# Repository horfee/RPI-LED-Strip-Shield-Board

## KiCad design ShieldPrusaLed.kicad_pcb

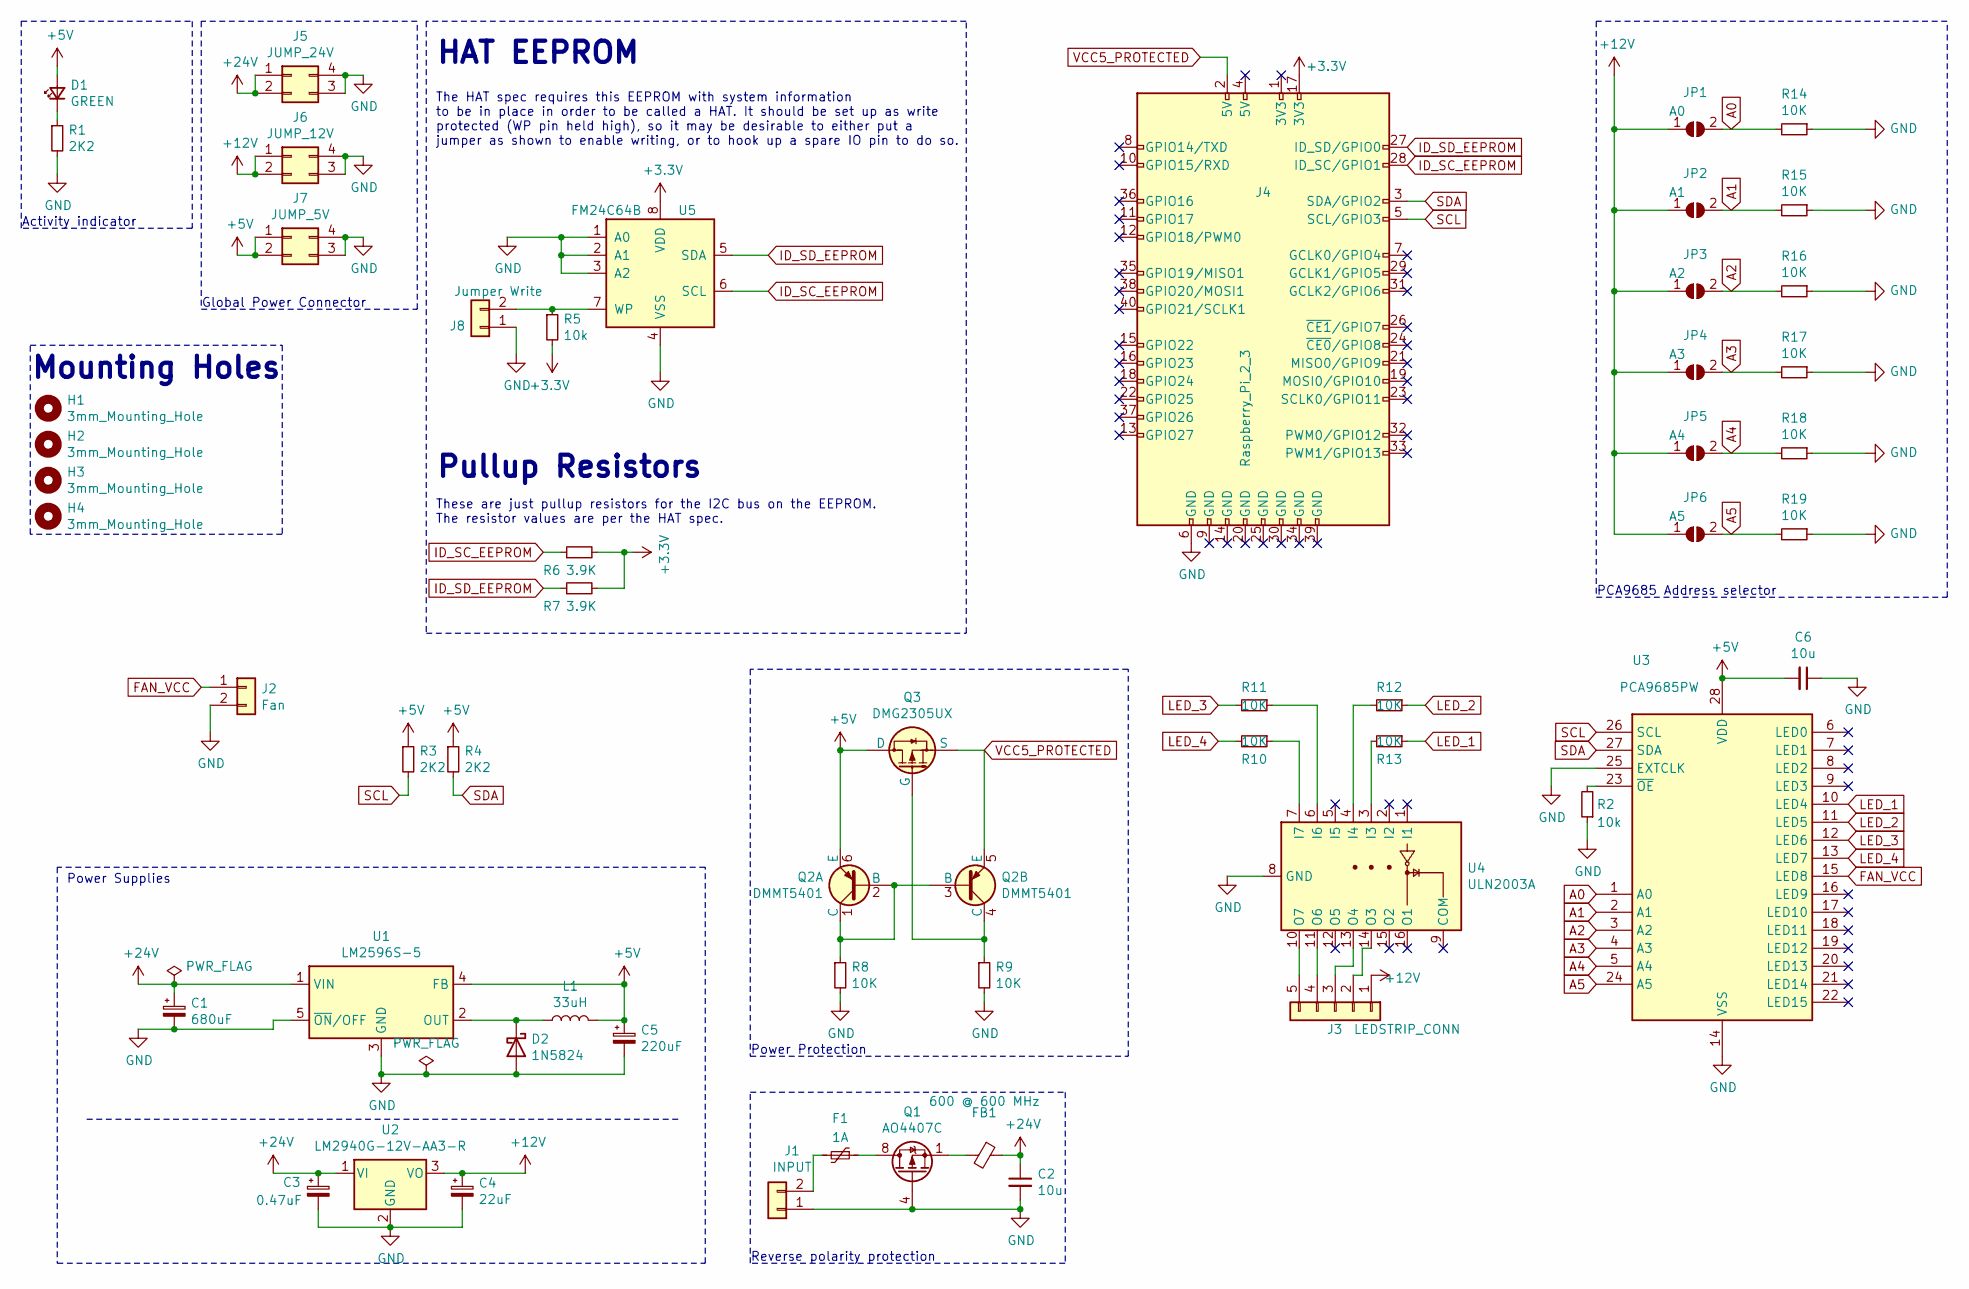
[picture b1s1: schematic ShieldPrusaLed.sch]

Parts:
C1: 680uF; CP_Radial_D10.0mm_P5.00mm_P7.50mm
C2, C6: 10u; C_0805_2012Metric
C3: 0.47uF; C_0603_1608Metric
C4: 22uF; C_0805_2012Metric
C5: 220uF; CP_Elec_6.3x5.4
D1: GREEN; LED_0603_1608Metric
D2: 1N5824; D_SMA
F1: 1A; Fuse_1206_3216Metric
FB1: 600 @ 600 MHz; R_0805_2012Metric
H1, H2, H3, H4: 3mm_Mounting_Hole; NPTH_3mm_ID
J1: INPUT; TerminalBlock_bornier-2_P5.08mm
J2: Fan; PinHeader_2x01_P2.54mm_Vertical_SMD
J3: LEDSTRIP_CONN; PinHeader_1x05_P2.54mm_Vertical_SMD_Pin1Left
J4: Raspberry_Pi_2_3; PinHeader_2x20_P2.54mm_Vertical_SMD
J5: JUMP_24V; PinHeader_2x02_P2.54mm_Vertical_SMD
J6: JUMP_12V; PinHeader_2x02_P2.54mm_Vertical_SMD
J7: JUMP_5V; PinHeader_2x02_P2.54mm_Vertical_SMD
J8: Jumper Write; PinHeader_2x01_P2.54mm_Vertical_SMD
JP1: A0; SolderJumper-2_P1.3mm_Open_RoundedPad1.0x1.5mm
JP2: A1; SolderJumper-2_P1.3mm_Open_RoundedPad1.0x1.5mm
JP3: A2; SolderJumper-2_P1.3mm_Open_RoundedPad1.0x1.5mm
JP4: A3; SolderJumper-2_P1.3mm_Open_RoundedPad1.0x1.5mm
JP5: A4; SolderJumper-2_P1.3mm_Open_RoundedPad1.0x1.5mm
JP6: A5; SolderJumper-2_P1.3mm_Open_RoundedPad1.0x1.5mm
L1: 33uH; L_12x12mm_H8mm
Q1: AO4407C; SOP-8_3.9x4.9mm_P1.27mm
Q2: DMMT5401; SOT-23-6
Q3: DMG2305UX; SOT-23
R1: 2K2; R_0402_1005Metric
R2, R5: 10k; R_0402_1005Metric
R3, R4: 2K2; R_0603_1608Metric
R6, R7: 3.9K; R_0603_1608Metric
R8, R9, R10, R11, R12, R13, R14, R15, R16, R17, R18, R19: 10K; R_0402_1005Metric
U1: LM2596S-5; TO-263-5_TabPin3
U2: LM2940G-12V-AA3-R; SOT-223
U3: PCA9685PW; TSSOP-28_4.4x9.7mm_P0.65mm
U4: ULN2003A; SOP-16_3.9x9.9mm_P1.27mm
U5: FM24C64B; SOIC-8_3.9x4.9mm_P1.27mm

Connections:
+3V3: J4.17 (3V3), R5.2, R6.2, R7.2, U5.8 (VDD); also elsewhere on the board
+5V: C5.1, C6.2, D1.2 (A), J7.1, J7.2, L1.2, Q2.6 (E), Q3.3 (D), R3.1, R4.1, U1.4 (FB), U3.28 (VDD)
+12V: C4.1, J3.1, J6.1, J6.2, JP1.1 (A), JP2.1 (A), JP3.1 (A), JP4.1 (A), JP5.1 (A), JP6.1 (A), U2.3 (VO)
+24V: C1.1, C2.1, C3.1, FB1.1, J5.1, J5.2, U1.1 (VIN), U2.1 (VI)
A0: JP1.2 (B), R14.2, U3.1 (A0)
A1: JP2.2 (B), R15.2, U3.2 (A1)
A2: JP3.2 (B), R16.2, U3.3 (A2)
A3: JP4.2 (B), R17.2, U3.4 (A3)
A4: JP5.2 (B), R18.2, U3.5 (A4)
A5: JP6.2 (B), R19.2, U3.24 (A5)
FAN_VCC: J2.1, U3.15 (LED8)
GND: C1.2, C2.2, C3.2, C4.2, C5.2, C6.1, D2.2 (A), J1.1, J2.2, J4.6 (GND), J5.3, J5.4, J6.3, J6.4, J7.3, J7.4, J8.1, Q1.4 (G), R1.2, R2.1, R8.2, R9.2, R14.1, R15.1, R16.1, R17.1, R18.1, R19.1, U1.3 (GND), U1.5 (~ON~/OFF), U2.2 (GND), U3.14 (VSS), U3.25 (EXTCLK), U4.8 (GND), U5.1 (A0), U5.2 (A1), U5.3 (A2), U5.4 (VSS); also elsewhere on the board
ID_SC_EEPROM: J4.28 (ID_SC/GPIO1), R6.1, U5.6 (SCL); also elsewhere on the board
ID_SD_EEPROM: J4.27 (ID_SD/GPIO0), R7.1, U5.5 (SDA); also elsewhere on the board
LED_1: R13.1, U3.10 (LED4)
LED_2: R12.1, U3.11 (LED5)
LED_3: R11.2, U3.12 (LED6)
LED_4: R10.2, U3.13 (LED7)
unnamed: D1.1 (K), R1.1
unnamed: D2.1 (K), L1.1, U1.2 (OUT)
unnamed: F1.1, Q1.8 (D)
unnamed: F1.2, J1.2
unnamed: FB1.2, Q1.1 (S)
unnamed: J3.2, U4.14 (O3)
unnamed: J3.3, U4.13 (O4)
unnamed: J3.4, U4.11 (O6)
unnamed: J3.5, U4.10 (O7)
unnamed 27: J4.1 (3V3); also elsewhere on the board
unnamed 28: J4.4 (5V); also elsewhere on the board
unnamed 29: J4.7 (GCLK0/GPIO4); also elsewhere on the board
unnamed 30: J4.8 (GPIO14/TXD); also elsewhere on the board
unnamed 31: J4.9 (GND); also elsewhere on the board
unnamed 32: J4.10 (GPIO15/RXD); also elsewhere on the board
unnamed 33: J4.11 (GPIO17); also elsewhere on the board
unnamed 34: J4.12 (GPIO18/PWM0); also elsewhere on the board
unnamed 35: J4.13 (GPIO27); also elsewhere on the board
unnamed 36: J4.14 (GND); also elsewhere on the board
unnamed 37: J4.15 (GPIO22); also elsewhere on the board
unnamed 38: J4.16 (GPIO23); also elsewhere on the board
unnamed 39: J4.18 (GPIO24); also elsewhere on the board
unnamed 40: J4.19 (MOSI0/GPIO10); also elsewhere on the board
unnamed 41: J4.20 (GND); also elsewhere on the board
unnamed 42: J4.21 (MISO0/GPIO9); also elsewhere on the board
unnamed 43: J4.22 (GPIO25); also elsewhere on the board
unnamed 44: J4.23 (SCLK0/GPIO11); also elsewhere on the board
unnamed 45: J4.24 (~CE0~/GPIO8); also elsewhere on the board
unnamed 46: J4.25 (GND); also elsewhere on the board
unnamed 47: J4.26 (~CE1~/GPIO7); also elsewhere on the board
unnamed 48: J4.29 (GCLK1/GPIO5); also elsewhere on the board
unnamed 49: J4.30 (GND); also elsewhere on the board
unnamed 50: J4.31 (GCLK2/GPIO6); also elsewhere on the board
unnamed 51: J4.32 (PWM0/GPIO12); also elsewhere on the board
unnamed 52: J4.33 (PWM1/GPIO13); also elsewhere on the board
unnamed 53: J4.34 (GND); also elsewhere on the board
unnamed 54: J4.35 (GPIO19/MISO1); also elsewhere on the board
unnamed 55: J4.36 (GPIO16); also elsewhere on the board
unnamed 56: J4.37 (GPIO26); also elsewhere on the board
unnamed 57: J4.38 (GPIO20/MOSI1); also elsewhere on the board
unnamed 58: J4.39 (GND); also elsewhere on the board
unnamed 59: J4.40 (GPIO21/SCLK1); also elsewhere on the board
unnamed: J8.2, R5.1, U5.7 (WP)
unnamed: Q2.1 (C), Q2.2 (B), Q2.3 (B), R8.1
unnamed: Q2.4 (C), Q3.1 (G), R9.1
unnamed: R2.2, U3.23 (~OE)
unnamed: R10.1, U4.7 (I7)
unnamed: R11.1, U4.6 (I6)
unnamed: R12.2, U4.4 (I4)
unnamed: R13.2, U4.3 (I3)
SCL: J4.5 (SCL/GPIO3), R3.2, U3.26 (SCL); also elsewhere on the board
SDA: J4.3 (SDA/GPIO2), R4.2, U3.27 (SDA); also elsewhere on the board
VCC5_PROTECTED: J4.2 (5V), Q2.5 (E), Q3.2 (S); also elsewhere on the board

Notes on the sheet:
Reverse polarity protection
Activity indicator
Power Supplies
Global Power Connector
HAT EEPROM
The HAT spec requires this EEPROM with system information to be in place in order to be called a HAT. It should be set up as write protected (WP pin held high), so it may be desirable to either put a jumper as shown to enable writing, or to hook up a spare IO pin to do so.
Pullup Resistors
These are just pullup resistors for the I2C bus on the EEPROM. The resistor values are per the HAT spec.
PCA9685 Address selector
Mounting Holes
Power Protection

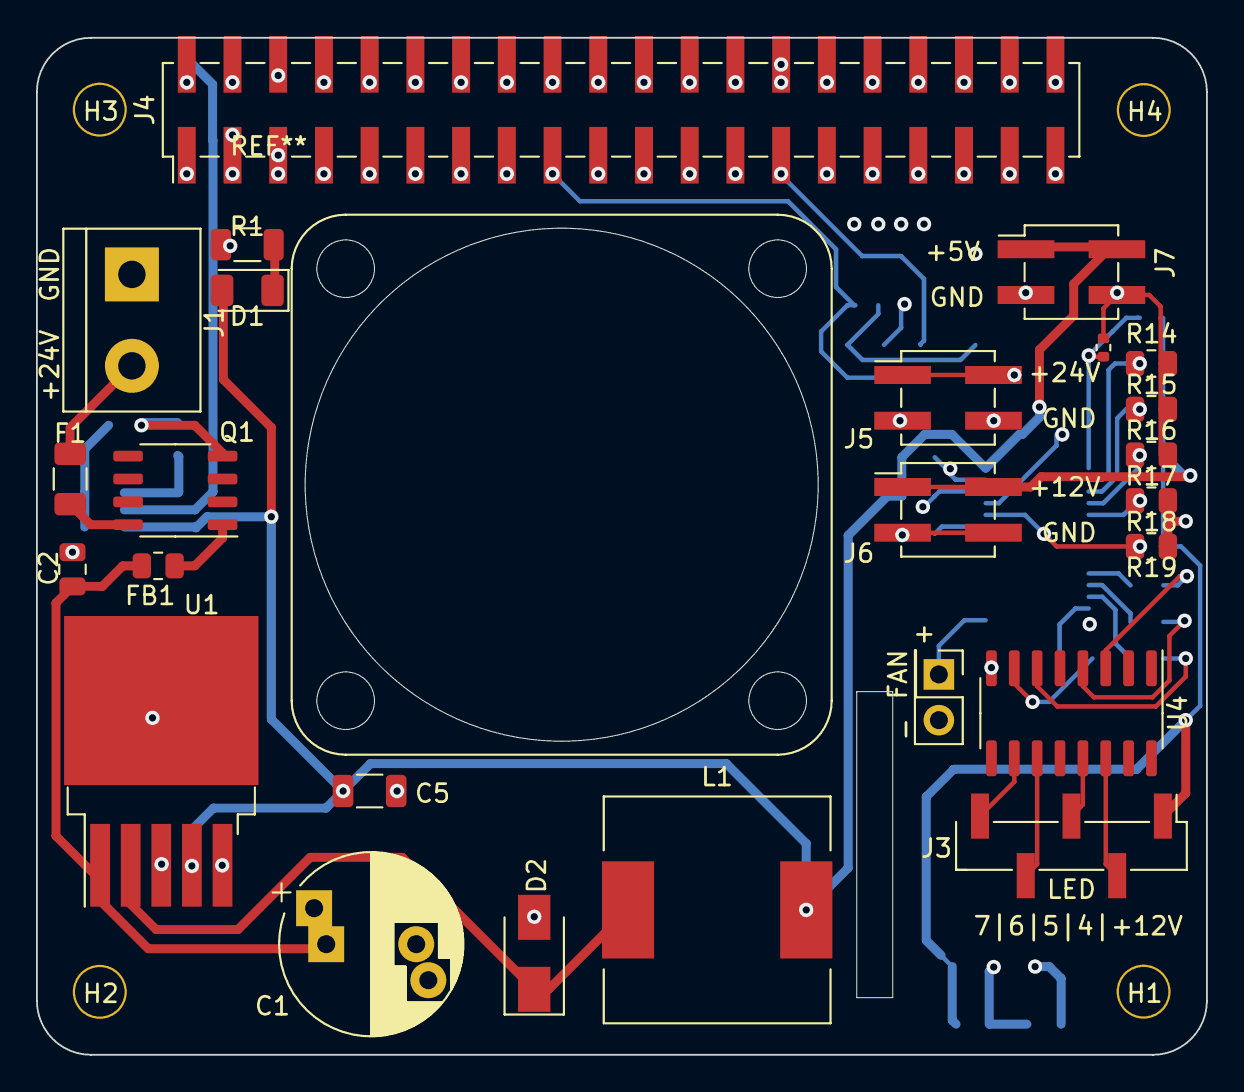
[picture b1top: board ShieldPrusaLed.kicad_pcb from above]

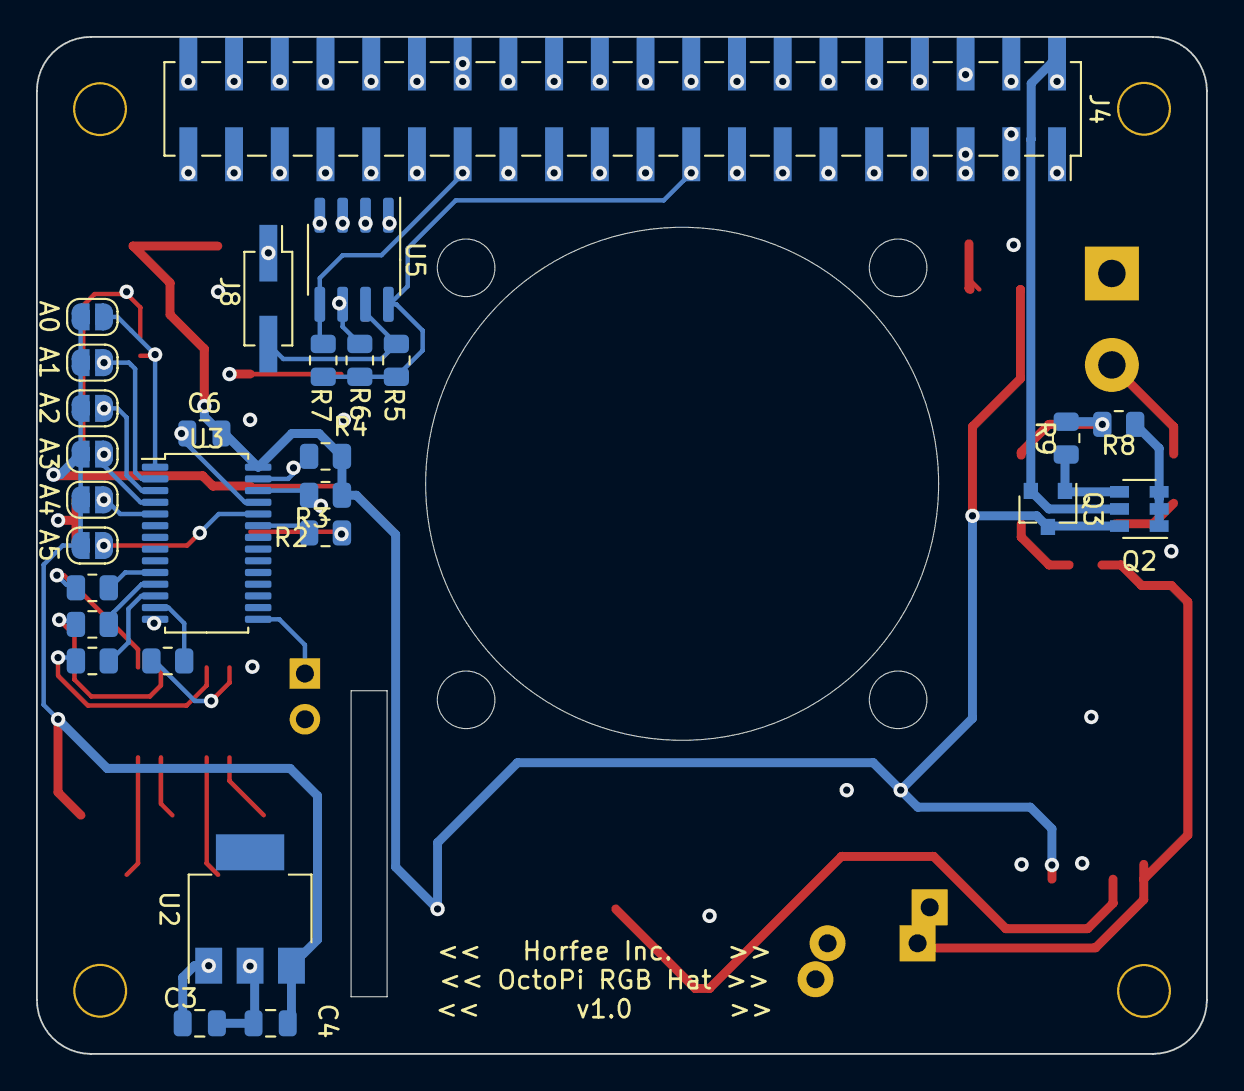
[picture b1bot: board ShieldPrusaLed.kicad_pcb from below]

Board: 4 copper layers, 65.0 x 56.5 mm, 57 parts (28 on the bottom side), 71 nets.

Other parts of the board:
J4#2: Raspberry_Pi_2_3; PinSocket_2x20_P2.54mm_Vertical_SMD

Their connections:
+3V3: J4#2.17; also elsewhere on the board
GND: J4#2.6; also elsewhere on the board
ID_SC_EEPROM: J4#2.28; also elsewhere on the board
ID_SD_EEPROM: J4#2.27; also elsewhere on the board
unnamed 27: J4#2.1; also elsewhere on the board
unnamed 28: J4#2.4; also elsewhere on the board
unnamed 29: J4#2.7; also elsewhere on the board
unnamed 30: J4#2.8; also elsewhere on the board
unnamed 31: J4#2.9; also elsewhere on the board
unnamed 32: J4#2.10; also elsewhere on the board
unnamed 33: J4#2.11; also elsewhere on the board
unnamed 34: J4#2.12; also elsewhere on the board
unnamed 35: J4#2.13; also elsewhere on the board
unnamed 36: J4#2.14; also elsewhere on the board
unnamed 37: J4#2.15; also elsewhere on the board
unnamed 38: J4#2.16; also elsewhere on the board
unnamed 39: J4#2.18; also elsewhere on the board
unnamed 40: J4#2.19; also elsewhere on the board
unnamed 41: J4#2.20; also elsewhere on the board
unnamed 42: J4#2.21; also elsewhere on the board
unnamed 43: J4#2.22; also elsewhere on the board
unnamed 44: J4#2.23; also elsewhere on the board
unnamed 45: J4#2.24; also elsewhere on the board
unnamed 46: J4#2.25; also elsewhere on the board
unnamed 47: J4#2.26; also elsewhere on the board
unnamed 48: J4#2.29; also elsewhere on the board
unnamed 49: J4#2.30; also elsewhere on the board
unnamed 50: J4#2.31; also elsewhere on the board
unnamed 51: J4#2.32; also elsewhere on the board
unnamed 52: J4#2.33; also elsewhere on the board
unnamed 53: J4#2.34; also elsewhere on the board
unnamed 54: J4#2.35; also elsewhere on the board
unnamed 55: J4#2.36; also elsewhere on the board
unnamed 56: J4#2.37; also elsewhere on the board
unnamed 57: J4#2.38; also elsewhere on the board
unnamed 58: J4#2.39; also elsewhere on the board
unnamed 59: J4#2.40; also elsewhere on the board
SCL: J4#2.5; also elsewhere on the board
SDA: J4#2.3; also elsewhere on the board
VCC5_PROTECTED: J4#2.2; also elsewhere on the board

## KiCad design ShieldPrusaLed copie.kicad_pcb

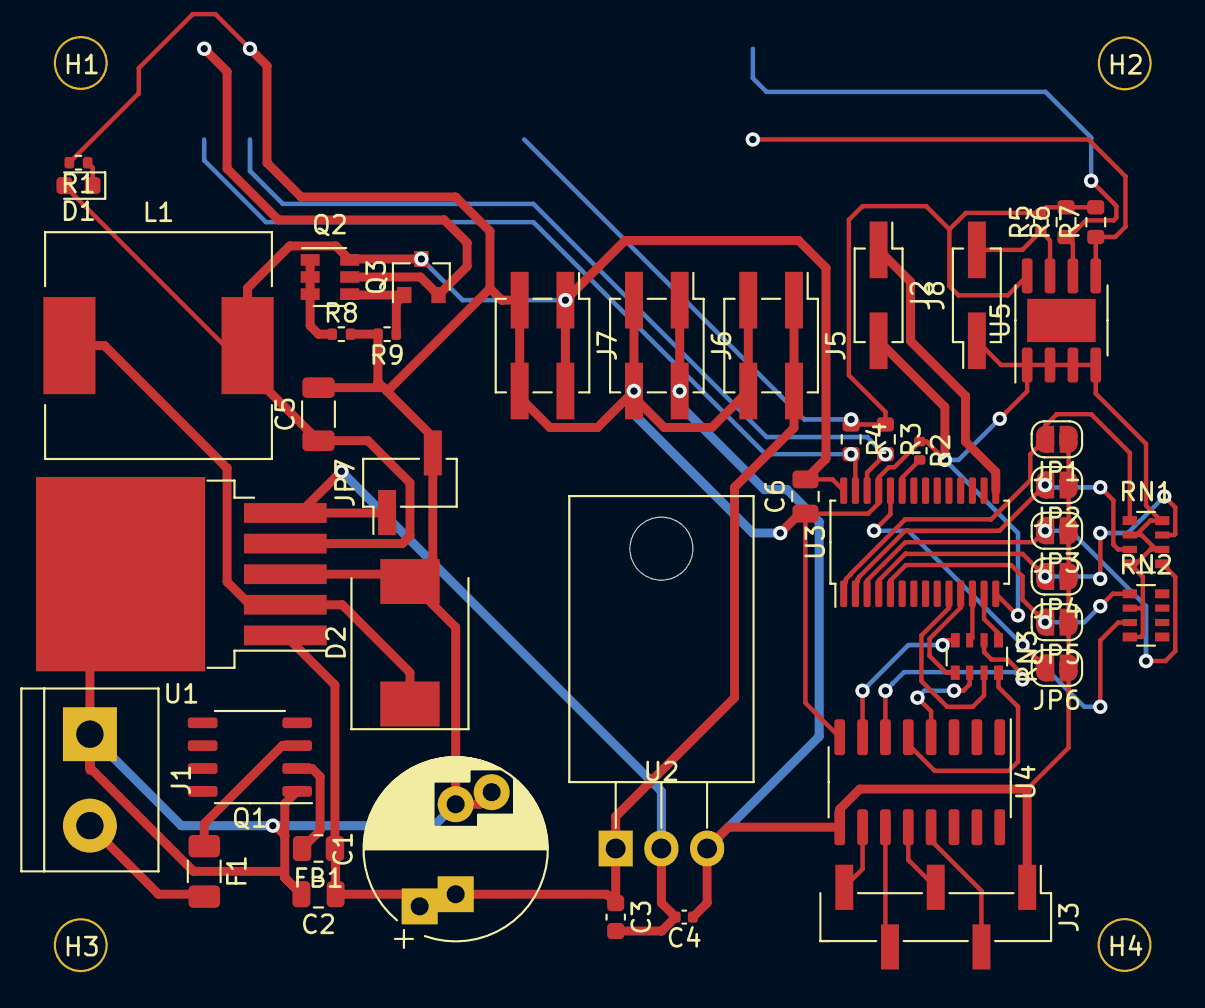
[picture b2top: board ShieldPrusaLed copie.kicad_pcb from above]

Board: 2 copper layers, 50 parts (1 on the bottom side), 39 nets.

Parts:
C1: 680uF; CP_Radial_D10.0mm_P5.00mm_P7.50mm
C2, C6: 10u; C_0805_2012Metric
C3: 0.33uF; C_0603_1608Metric
C4: 0.1uF; C_0402_1005Metric
C5: 220uF; C_1206_3216Metric
D1: GREEN; LED_0603_1608Metric
D2: 1N5824; D_SMC
F1: 1A; Fuse_1206_3216Metric
FB1: 600 @ 600 MHz; R_0805_2012Metric
H1, H2, H3, H4: 3mm_Mounting_Hole; NPTH_3mm_ID
J1: INPUT; TerminalBlock_bornier-2_P5.08mm
J2: Fan; PinHeader_2x01_P2.54mm_Vertical_SMD
J3: LEDSTRIP_CONN; PinHeader_1x05_P2.54mm_Vertical_SMD_Pin1Left
J4: Raspberry_Pi_2_3; PinSocket_2x20_P2.54mm_Vertical_SMD
J5: JUMP_24V; PinHeader_2x02_P2.54mm_Vertical_SMD
J6: JUMP_12V; PinHeader_2x02_P2.54mm_Vertical_SMD
J7: JUMP_5V; PinHeader_2x02_P2.54mm_Vertical_SMD
J8: Jumper Write; PinHeader_2x01_P2.54mm_Vertical_SMD
JP1: SJ_A0; SolderJumper-2_P1.3mm_Open_RoundedPad1.0x1.5mm
JP2: SJ_A1; SolderJumper-2_P1.3mm_Open_RoundedPad1.0x1.5mm
JP3: SJ_A2; SolderJumper-2_P1.3mm_Open_RoundedPad1.0x1.5mm
JP4, JP5, JP6: SJ_A3; SolderJumper-2_P1.3mm_Open_RoundedPad1.0x1.5mm
JP7: Jumper_2_Bridged; PinHeader_1x02_P2.54mm_Vertical_SMD_Pin1Left
L1: 33uH; L_12x12mm_H8mm
Q1: AO4407C; SOP-8_3.9x4.9mm_P1.27mm
Q2: DMMT5401; SOT-23-6
Q3: DMG2305UX; SOT-23
R1: 470; R_0402_1005Metric
R2, R5: 10k; R_0402_1005Metric
R3, R4: 2K2; R_0603_1608Metric
R6, R7: 3.9K; R_0603_1608Metric
R8, R9: 10K; R_0402_1005Metric
RN1, RN2, RN3: 10k; R_Array_Convex_4x0603
U1: LM2596S-5; TO-263-5_TabPin3
U2: LM7812_TO220; TO-220-3_Horizontal_TabDown
U3: PCA9685PW; TSSOP-28_4.4x9.7mm_P0.65mm
U4: ULN2003A; SOP-16_3.9x9.9mm_P1.27mm
U5: CAT24C32; SOIC-8-1EP_3.9x4.9mm_P1.27mm_EP2.41x3.81mm

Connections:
+3V3: J4.1, J4.17, R3.1, R4.1, R5.2, R6.2, R7.2, U5.8
+5V: C5.1, C6.2, D1.2, J7.1, J7.2, L1.2, Q2.6, Q3.3, U1.4, U3.28
+12V: C4.1, J3.1, J6.1, J6.2, JP1.1, JP2.1, JP3.1, JP4.1, JP5.1, JP6.1, U2.3, U4.9
+24V: C1.1, C2.1, C3.1, FB1.1, J5.1, J5.2, U1.1, U2.1
/SWITCHABLE_GND: C3.2, C4.2, JP7.1, U1.5, U2.2
A0: JP1.2, RN1.1, U3.1
A1: JP2.2, RN1.3, U3.2
A2: JP3.2, RN1.5, U3.3
A3: JP4.2, RN1.7, U3.4
A4: JP5.2, RN2.1, U3.5
A5: JP6.2, RN2.3, U3.24
FAN_VCC: J2.1, U3.15
GND: C1.2, C2.2, C5.2, C6.1, D2.2, J1.1, J2.2, J4.6, J5.3, J5.4, J6.3, J6.4, J7.3, J7.4, J8.1, JP7.2, Q1.1, R1.2, R2.1, R8.2, R9.2, RN1.2, RN1.4, RN1.6, RN1.8, RN2.2, RN2.4, U1.3, U3.14, U3.25, U4.8, U5.1, U5.2, U5.3, U5.4
ID_SC_EEPROM: J4.28, R6.1, U5.6
ID_SD_EEPROM: J4.27, R7.1, U5.5
LED_B: RN3.3, U3.12
LED_G: RN3.5, U3.11
LED_R: RN3.7, U3.10
LED_W: RN3.1, U3.13
unnamed: D1.1, R1.1
unnamed: D2.1, L1.1, U1.2
unnamed: F1.1, Q1.3
unnamed: F1.2, J1.2
unnamed: FB1.2, Q1.2
unnamed: J3.2, U4.13
unnamed: J3.3, U4.12
unnamed: J3.4, U4.11
unnamed: J3.5, U4.10
unnamed: J8.2, R5.1, U5.7
unnamed: Q2.1, Q2.2, Q2.3, R8.1
unnamed: Q2.4, Q3.1, R9.1
unnamed: R2.2, U3.23
unnamed: RN3.2, U4.6
unnamed: RN3.4, U4.7
unnamed: RN3.6, U4.4
unnamed: RN3.8, U4.5
SCL: J4.5, R3.2, U3.26
SDA: J4.3, R4.2, U3.27
VCC5_PROTECTED: J4.2, J4.4, Q2.5, Q3.2

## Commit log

2021-09-10 3D View fix
